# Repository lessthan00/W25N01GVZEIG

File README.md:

# W25N01GVZEIG board change from W25Q80VSSIG_b

接口定义  
1-CS#->SPI_CS#  
2-DO(IO1)->SPI_MISO  
3-WP#(IO2)  
4-GND  
5-DI(IO0)->SPI_MOSI  
6-CLK->SPI_CLK  
7-HOLD#(IO3)  
8-VCC  
9-EP

NAND flash
tBE 2ms
memory 1Gbit
SPI
数据保留时间TDR 10year
Tpp 250us
package WSON-8-EP(6.1x8)

## W25Q80VSSIG_b

模块接口定义从从接口标准顺序出发
比如stm32f103的SPI1
VSS  
GND  
PA4 SPI1_NSS    CS#  
PA5 SPI1_SCK    CLK  
PA7 SPI1_MOSI   DI(IO0)  
PA6 SPI1_MISO   DO(IO1)  
                WP#(IO2)  
                HOLD#(IO4)  

## W25Q80VSSIG_a  

[W25Q80VSSIG](https://www.jlc-smt.com/lcsc/detail?componentCode=C14086)  

class   NOR FLASH  
package     SOIC-8-208mil  
memory  8Mbit  
interface   dual and quad spi  
檫除时间tBE     150mS@64KB  
fc  104Mhz  
写入时间Tpp     3ms  

接口定义  
1-CS#->SPI_CS#  
2-DO(IO1)->SPI_MISO  
3-WP#(IO2)   
4-GND  
5-DI(IO0)->SPI_MOSI  
6-CLK->SPI_CLK  
7-HOLD#(IO3)   
8-VCC  

[模块参考](https://item.taobao.com/item.htm?priceTId=undefined&utparam=%7B%22aplus_abtest%22%3A%226a56d4f83e5146ee0d4dd8b8974ab268%22%7D&id=660467426297&ns=1&abbucket=4&xxc=taobaoSearch&detail_redpacket_pop=true&query=flash+%E6%A8%A1%E5%9D%97&skuId=5631050961877&spm=a21n57.1.hoverItem.5&ltk2=1746922057202bi5ueergtsso7z386oxzxf)   

模块接口定义  
VCC CS DO GND CLK DI  

## GD25Q32CSIG_a board = W25Q80VSSIG_a  

## GD25Q32CSIG_b board = W25Q80VSSIG_b

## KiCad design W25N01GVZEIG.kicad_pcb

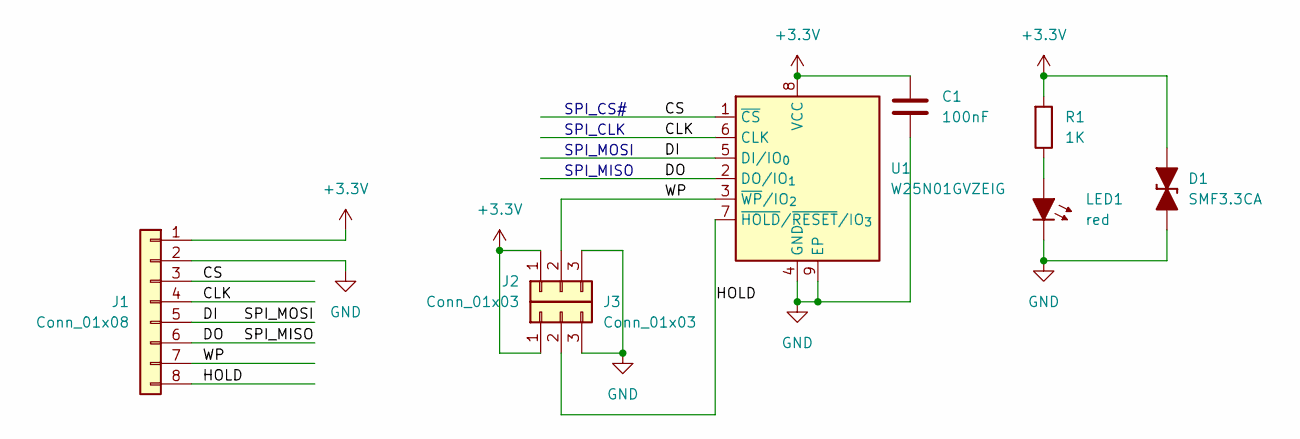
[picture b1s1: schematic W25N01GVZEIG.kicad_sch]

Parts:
C1: 100nF; C_1206_3216Metric
D1: SMF3.3CA; D_SOD-123F
J1: Conn_01x08; PinHeader_1x08_P2.54mm_Vertical
J2, J3: Conn_01x03; PinHeader_1x03_P2.54mm_Vertical
LED1: red; LED_1206_3216Metric
R1: 1K; R_1206_3216Metric
U1: W25N01GVZEIG; WSON-8-1EP_8x6mm_P1.27mm_EP3.4x4.3mm

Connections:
+3.3V: C1.1, D1.2 (A), J1.1, J2.1, J3.1, R1.1, U1.8 (VCC)
/CLK: J1.4, U1.6 (CLK)
/CS: J1.3, U1.1 (~CS)
/DI: J1.5, U1.5 (DI/IO_{0})
/DO: J1.6, U1.2 (DO/IO_{1})
/HOLD: J1.8, J3.2, U1.7 (~HOLD/~RESET/IO_{3})
/WP: J1.7, J2.2, U1.3 (~WP/IO_{2})
GND: C1.2, D1.1 (K), J1.2, J2.3, J3.3, LED1.1 (K), U1.4 (GND), U1.9 (EP)
unnamed: LED1.2 (A), R1.2

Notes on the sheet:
SPI_CS#
SPI_CLK
SPI_MOSI
SPI_MISO

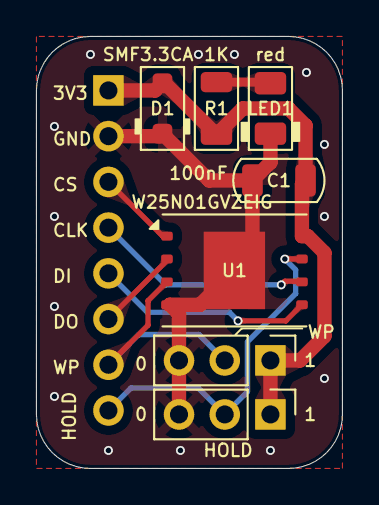
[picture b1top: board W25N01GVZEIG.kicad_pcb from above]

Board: 2 copper layers, 17.0 x 24.0 mm, 8 parts (1 on the bottom side), 9 nets.
